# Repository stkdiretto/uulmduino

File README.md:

# uulmduino

Eine Mischung aus Arduino (besser gesagt dem [Diavolino von Evil Mad Scientist Labs](http://www.evilmadscientist.com/2010/diavolino/)) und der [TV-B-Gone-Version von Ken Shirriff](https://github.com/shirriff/Arduino-TV-B-Gone). Auf Basis des Diavolino und mit Hilfe des [Sparkfun Inventors' Kit](https://www.sparkfun.com/products/12060) von der [Arbeitsgruppe WissenSchaffer](http://www.uni-ulm.de/in/fakultaet/studieninteressierte/wissenschaffer.html) entwickelt für den Girls'Day 2015 an der Uni Ulm.

## Handbuch bauen

Das Handbuch ist [im Ordner "handbuch"](handbuch/) und liegt als Markdown vor. Es kann mit Pandoc nach PDF exportiert werden:

`pandoc anleitung.md -o anleitung.pdf --latex-engine=xelatex --variable geometry="a5paper" --variable mainfont="Droid Sans"`

Wer das Projekt nachmachen möchte, findet im handbuch-Ordner auch eine skizzenhafte Anleitung, was hinter den Kulissen passieren muss. Pull-Requests zur Verbesserung sind gerne gesehen!

## Dankeschöns

 * Leiterplattentechnik der Uni Ulm für die gute Beratung und die Platinenfertigung
 * Maria Aufheimer, Robien Baldrich, Dominic Meißner, David-1 Schmid für Bugfixing und Input
 * Juliane Wessalowski für den Betatest
 * Alle Beitragenden, deren Basismaterial unter Freier Lizenz wir verwenden durften!

## Changelog
 * 2015-04-22 Erste Version
 * 2015-04-22 Übersetzte Experimente aus dem SIK hinzugefügt
 * 2015-04-22 KiCad-Quellen hinzugefuegt
 * 2015-08-26 Revision 2 mit umfangreicherererer KiCad-Quellenlage und einigen gefixten Fehlern. Noch nicht praxiserprobt!
 * 2015-11-16 Fehler in rev2 vermerkt und [BOM](bom.md) hinzugefügt, Fehler im Handbuch korrigiert
 * 2016-04-12 Erster Aufschlag einer [Anleitung für KursleiterInnen](handbuch/fuer%20kursleiter_innen.md)

## Bekannte Fehler (Revision 2)
 * Bei allen Transistoren sind B und E vertauscht :(

## Bekannte Fehler (Revision 1, veraltet)
 * IR-Sender ist auf dem Board mit Pin 9 verbunden → Sollte Pin 10 sein (Fixed in rev2)
 * DC-In-Buchse hat Masse auf dem mittleren Pin, sollte eigentlich andersherum sein (Fixed in rev2)
 * Bohrlöcher für die Zugentlastung der Batteriekastenzuleitungen sind zu klein (Fixed in rev2)
 * Beschriftungen könnten besser sein (Sort of fixed in rev2)
 * KiCad-Files sind sehr unorganisiert (Sort of fixed in rev2)

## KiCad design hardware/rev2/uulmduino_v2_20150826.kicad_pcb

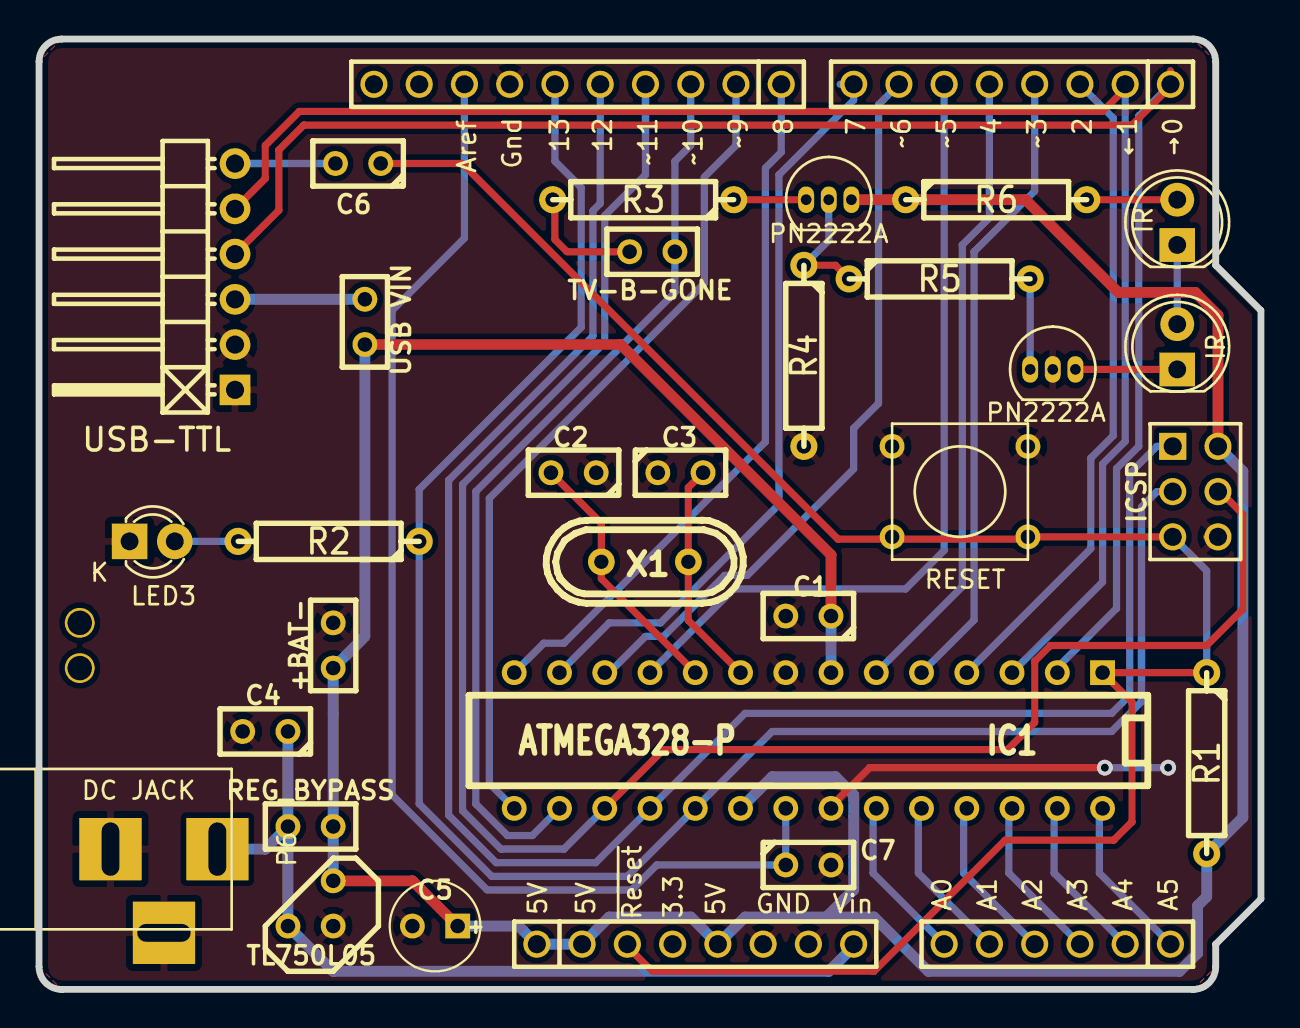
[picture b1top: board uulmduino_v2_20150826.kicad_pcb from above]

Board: 2 copper layers, 68.6 x 53.3 mm, 35 parts (0 on the bottom side), 37 nets.

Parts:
1PIN, 1PIN#2: P***; 1pin_mechanical
+BAT-: BATTERY IN; SIL-2
C1, C4, C6, C7: 0.1µF; C1
C2, C3: 18pF; C1
C5: 10µF; C1V5
IC1: ATMEGA328-P; DIP-28__300
ICSP: CONN_3X2; pin_array_3x2
LED1, LED2: IR; LED-5MM
LED3: PIN13; LED-3MM
P1: CONN_10; HEADER_100MIL_1R10P_PTH
P2, P4: CONN_8; HEADER_100MIL_1R8P_PTH
P3: CONN_6; HEADER_100MIL_1R6P_PTH
P6: DC JACK; BARREL_JACK
Q1, Q2: PN2222A; TO-92_Inline_Narrow_Oval
R1, R4: 10k; R4
R2: 1k; R4
R3: R; R4
R5: 100; R4
R6: 220; R4
REG_BYPASS: Regulator bypass; SIL-2
SW1: RESET; SW_PUSH_SMALL
TV-B-GONE: TV_B_GONE; SIL-2
U1: TL750L05; LM78XX-TO92
USB VIN: VCC USB; SIL-2
USB-TTL: CONN_6; Pin_Header_Angled_1x06
X1: 16 MHz; Crystal_HC49-U_Vertical

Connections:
5V: +BAT-.1, C1.1, C5.1, IC1.7, IC1.20, ICSP.2, P4.1, P4.2, P4.5, Q1.3, R1.2, R6.1, REG_BYPASS.2, U1.VO, USB VIN.2
AD0: IC1.23, P3.6
AD1: IC1.24, P3.5
AD2: IC1.25, P3.4
AD3: IC1.26, P3.3
AD4/SDA: IC1.27, P3.2
AD5/SCL: IC1.28, P3.1
AREF: C7.1, IC1.21, P1.8
GND: +BAT-.2, C1.2, C2.1, C3.1, C4.2, C5.2, C7.2, IC1.8, IC1.22, ICSP.6, LED3.1, P1.7, P4.6, P4.7, P6.2, P6.3, Q2.2, R4.2, SW1.1, U1.GND, USB-TTL.1, USB-TTL.2
IO0: IC1.2, P2.1, USB-TTL.4
IO1: IC1.3, P2.2, USB-TTL.5
IO2: IC1.4, P2.3
IO3: IC1.5, P2.4
IO4: IC1.6, P2.5
IO5: IC1.11, P2.6
IO6: IC1.12, P2.7
IO7: IC1.13, P2.8
IO8: IC1.14, P1.1
IO9: IC1.15, P1.2
IO10/SS: IC1.16, P1.3, TV-B-GONE.1
IO11/MOSI: IC1.17, ICSP.4, P1.4
IO12/MISO: IC1.18, ICSP.1, P1.5
IO13/SCK: IC1.19, ICSP.3, P1.6, R2.1
unnamed: C2.2, IC1.10, X1.2
unnamed: C3.2, IC1.9, X1.1
unnamed: C6.2, USB-TTL.6
unnamed: USB VIN.1, USB-TTL.3
unnamed: R3.2, TV-B-GONE.2
unnamed: LED1.1, LED2.2
unnamed: LED1.2, R6.2
unnamed: LED2.1, Q2.3
unnamed: LED3.2, R2.2
unnamed: Q1.1, R3.1
unnamed: Q1.2, R4.1, R5.1
unnamed: Q2.1, R5.2
RESET: C6.1, IC1.1, ICSP.5, P4.3, R1.1, SW1.2
VIN: C4.1, P4.8, P6.1, REG_BYPASS.1, U1.VI

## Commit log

2015-04-22 Erste Version, Girls'Day 2015
2015-04-22 uebersetzten Code fuer Schaltkreis 1 aus dem SIK hinzugefuegt
2015-04-22 KiCad-Files
2015-04-22 uebersetzter Versuch 2
2015-08-26 added revision 2 of the board
    This revised version of the uulmduino board should fix the following issues:
    * correct polarity for DC jack
    * TV-B-Gone-Input wired to Pin 10 instead of Pin 9
    * larger NPTH for battery holder strain relief
2015-11-16 Errata ergaenzt, BOM hinzugefuegt
    Fehler in Rev 2: Transistor-Footprint falsch ;(
2015-11-25 Fixed omissions in BOM, clarified descriptions in handbook
2015-11-25 Re-rendered PDF for manual; BOM extended
2015-12-02 reorganized arduino INO files for compatibility w/ IDE
2016-04-12 added kursleiter handbuch first draft
2018-10-11 Update einkaufslistengenerator
    wrong reichelt article number for atmega
2020-07-15 maybe this fixes the link
2020-07-15 maybe _this_ fixes the link
2020-07-15 updated link to ateval board
2022-02-23 Update fuer kursleiter_innen.md
    linkfix ateval
